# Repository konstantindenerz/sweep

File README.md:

# Sweep

## Hint to this repo

The reason for this fork is the custom themed `Sweep High (Synthwave)`:

## Original

| Front | Back |
| :---: | :---: |
|  |  |

<span>

</span>

## What is sweep?

Sweep is a version of the more fabulous [Ferris](https://github.com/pierrechevalier83/ferris) by [Pierre Chevalier](https://github.com/pierrechevalier83/) that uses a daughter board like a promicro, elite-c, bit-c, nice!nano etc. instead of using onboard components.

## What are the different types?

| Device | On/Off Switch<sup>[1]</sup> | Reversible PCB<sup>[2]</sup> | Choc V1 | Choc V2 | Choc Mini | MX & Alps | Choc Spacing<sup>[3]</sup> | Tenting<sup>[4]</sup> | Hot Swap |
| :--- | :---: | :---: | :---: | :---: | :---: | :---: | :---: | :---: | :---: |
| Sweep2.x          | ✔ |   | ✔ |   |   |   | ✔ | ✔ | Mill-Max (optional) |
| Sweep Bling LP    | ✔ |   | ✔ |   |   |   | ✔ | ✔ | Kailh (required) |
| Sweep Bling MX    | ✔ | ✔ |   |   |   | ⚠<br/><sup>[5]</sup> |   | ✔ | Kailh (required) |
| Sweep High        | ✔ |   | ✔ | ✔ |   | ✔ |   | ✔ |
| Sweep Half Swept  | ✔ | ✔ | ✔ |   |   |   | ✔ | ✔ | Mill-Max (optional) |
| Sweep Compact Low |   | ✔ |   |   | ✔ |   | ✔ |   |

> Note: All versions support bluetooth with Nice!Nano

*<sup>[1]</sup> An on/off switch is recommended for bluetooth builds.*  
*<sup>[2]</sup> With a reversible PCB it's easier to make mistakes during assembly, but it allows you to purchase less boards.*  
*<sup>[3]</sup> Choc spaced boards have the switches in a tighter grid. This provides a better final look but is only compatible with some choc keycaps. (e.g. MBK)*  
*<sup>[4]</sup> Supports splitkb's [tenting puck.](https://splitkb.com/products/tenting-puck?_pos=1&_psq=tenting%20&_ss=e&_v=1.0)*  
*<sup>[5]</sup> MX + kailh hotswap ONLY. Alps are NOT supported.*  

* Sweep2 - Recommended Choc v1 board with all the features.
* Sweep Bling MX - An MX only Sweep that features Kailh's hotswap sockets and a stacked case.
* Sweep High - Same as the Sweep2 but trades choc spacing for compatibility with more switches and keycaps.
* Sweep Half Swept - Half of a Sweep2 with double pro-micro footprint (letting you avoid having one daughter-board flipped upside-down)
* Sweep Compact Low - The only version that supports Choc minis.

## Components list

To build and use a Sweep you will need:

* 1x PCB Kit
* 2x promicro compatible boards or 2 nice!nanos.
* 34 switches of a compatible type (refer to the compatibility table)
* 34 keycaps
* 2x reset switches (optional; [B3U-1000P(M)](https://github.com/davidphilipbarr/Sweep/issues/20))
* Some little rubber feet/bumpers
* 2x power switches (optional if supported; MSK 12C02)
* 1x TRRS (not TRS!) cable (wired build only)
* 2x TRRS Jack [PJ-320A] (wired build only)
* 1 USB Cable (depends on your micro-controller choice)

## How do I make this thing?

## Firmware

The firmware can be found [with the Ferris  firmware as part of QMK](https://github.com/qmk/qmk_firmware/tree/master/keyboards/ferris/sweep).

Firmware for zmk and bluemicro_ble is called ["Cradio"](https://zmk.dev/docs/hardware/).

## Who made this?

* [Pierre Chevalier](https://github.com/pierrechevalier83)
* [David Barr](https://github.com/davidphilipbarr)
* [Ibnu Daru Aji](https://github.com/ibnuda/)
* [Duccio](https://github.com/duckyb)

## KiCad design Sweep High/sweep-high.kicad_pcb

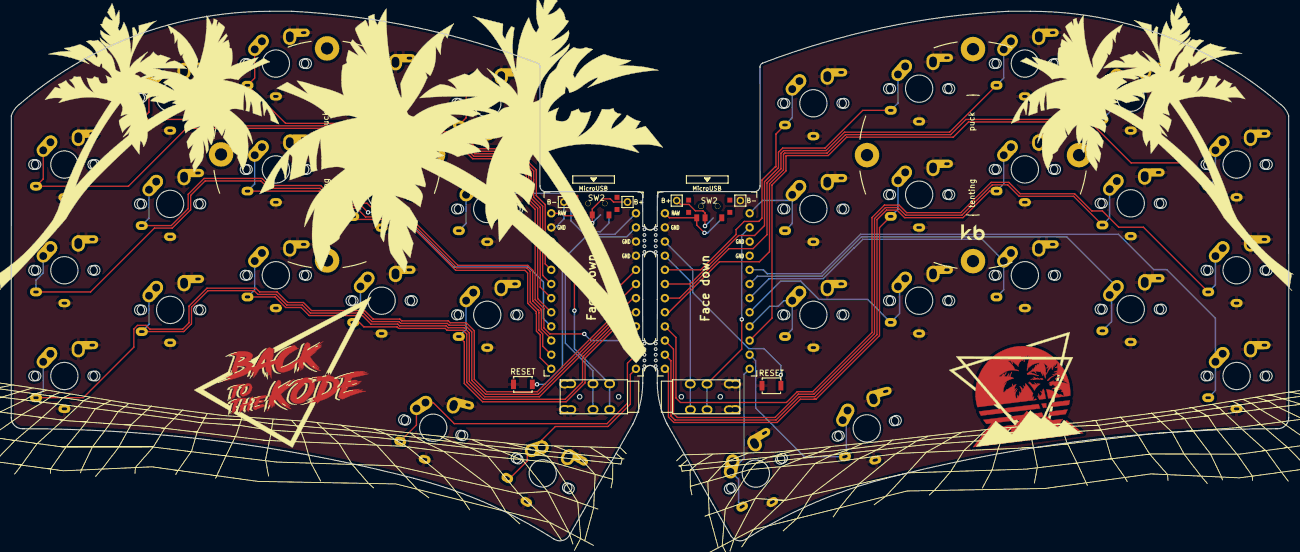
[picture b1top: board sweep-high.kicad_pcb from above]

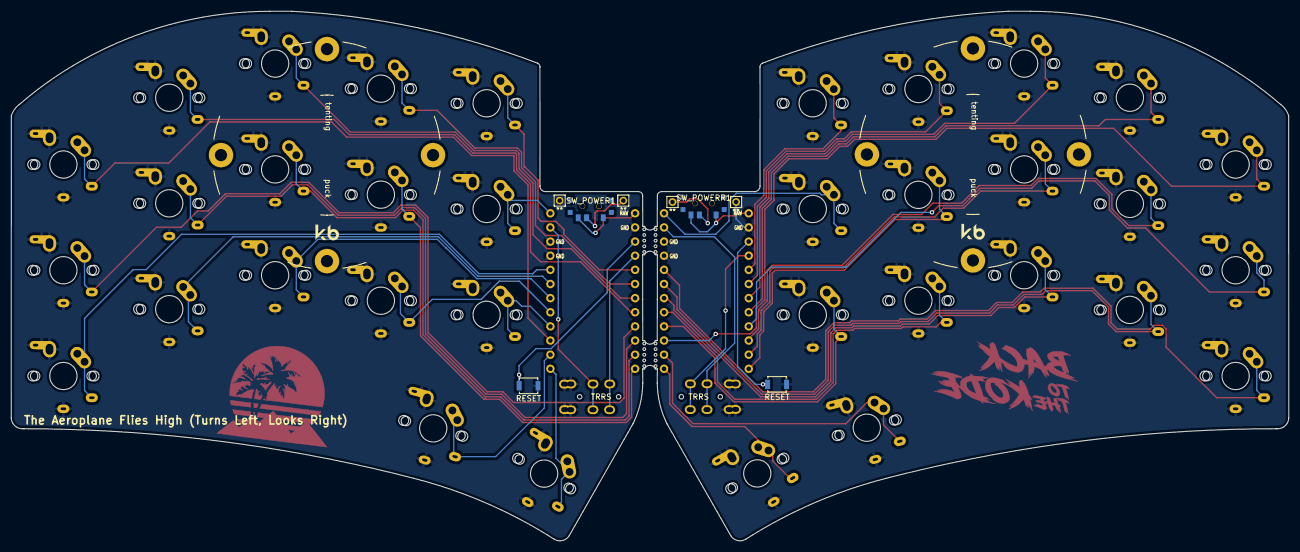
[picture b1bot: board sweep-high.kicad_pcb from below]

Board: 2 copper layers, 229.5 x 95.2 mm, 52 parts (4 on the bottom side), 43 nets.

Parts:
B+: MountingHole_Pad; 1pin_conn
B+#2: MountingHole_Pad; 1pin_conn
B-: MountingHole_Pad; 1pin_conn
B-#2: MountingHole_Pad; 1pin_conn
J1, J2: AudioJack4dpb; TRRS-PJ-DPB2
RSW1, RSW1#2, RSW2, RSW2#2: SW_Push; SW_SPST_B3U-1000P
SW2, SW2_r1, SW3, SW3_r1, SW4, SW4_r1, SW5, SW5_r1, SW6, SW6_r1, SW7_r1, SW8, SW8_r1, SW9, SW9_r1, SW10, SW11, SW11_r1, SW12, SW12_r1, SW13_r1, SW14, SW15, SW15_r1, SW16, SW16_r1, SW17, SW17_r1, SW18, SW18_r1, SW20, SW20_r1, SW21, SW21_r1: SW_Push; keyswitch_cherrymx_alps_choc12_slots_1u
SW2#2, SW2#3: SW_SPDT; SPDT_C128955r
SW_POWER1: SW_SPDT; SPDT_C128955
SW_POWERR1: SW_SPDT; SPDT_C128955
U1, U2: ProMicro-kbd; ProMicro_v3_min
mouse-bite-5mm-slot, mouse-bite-5mm-slot#2: VAL**; mouse-bite-5mm-slot-with-space-for-track

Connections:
BT+: B+#2.1, SW2#3.2, SW_POWER1.2
BT+_r: B+.1, SW2#2.2, SW_POWERR1.2
Switch1: SW2.1, U1.10
Switch1_r: SW2_r1.1, U2.10
Switch2: SW3.1, U1.17
Switch2_r: SW3_r1.1, U2.17
Switch3: SW4.1, U1.18
Switch3_r: SW4_r1.1, U2.18
Switch4: SW5.1, U1.19
Switch4_r: SW5_r1.1, U2.19
Switch5: SW6.1, U1.20
Switch5_r: SW6_r1.1, U2.20
Switch6: SW8.1, U1.16
Switch6_r: SW7_r1.1, U2.16
Switch7: SW9.1, U1.15
Switch7_r: SW8_r1.1, U2.15
Switch8: SW10.1, U1.14
Switch8_r: SW9_r1.1, U2.14
Switch9: SW11.1, U1.13
Switch9_r: SW11_r1.1, U2.13
Switch10: SW12.1, U1.1
Switch10_r: SW12_r1.1, U2.1
Switch11: SW14.1, U1.5
Switch11_r: SW13_r1.1, U2.5
Switch12: SW15.1, U1.6
Switch12_r: SW18_r1.1, U2.6
Switch13: SW16.1, U1.7
Switch13_r: SW15_r1.1, U2.7
Switch14: SW17.1, U1.8
Switch14_r: SW16_r1.1, U2.8
Switch15: SW18.1, U1.9
Switch15_r: SW17_r1.1, U2.9
Switch16: SW21.1, U1.11
Switch16_r: SW21_r1.1, U2.11
Switch17: SW20.1, U1.12
Switch17_r: SW20_r1.1, U2.12
Switch18: J2.R1, U1.2
Switch18_r: J1.R1, U2.2
gnd: B-.1, B-#2.1, J1.S, J1.T, J2.S, J2.T, RSW1.1, RSW1#2.1, RSW2.1, RSW2#2.1, SW2.2, SW2_r1.2, SW3.2, SW3_r1.2, SW4.2, SW4_r1.2, SW5.2, SW5_r1.2, SW6.2, SW6_r1.2, SW7_r1.2, SW8.2, SW8_r1.2, SW9.2, SW9_r1.2, SW10.2, SW11.2, SW11_r1.2, SW12.2, SW12_r1.2, SW13_r1.2, SW14.2, SW15.2, SW15_r1.2, SW16.2, SW16_r1.2, SW17.2, SW17_r1.2, SW18.2, SW18_r1.2, SW20.2, SW20_r1.2, SW21.2, SW21_r1.2, U1.3, U1.4, U1.23, U2.3, U2.4, U2.23
raw: SW2#2.3, SW2#3.3, SW_POWER1.3, SW_POWERR1.3, U1.24, U2.24
reset: RSW1.2, RSW1#2.2, U1.22
reset_r: RSW2.2, RSW2#2.2, U2.22
vcc: J1.R2, J2.R2, U1.21, U2.21

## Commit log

2022-09-03 feat(synthwave): add palms and sun
2022-09-03 Update gallery (automated)
2022-09-03 changed preview styles
2022-09-03 update preview
2022-09-04 update left side branding
2022-09-04 update left side
2022-09-04 create new sweep high copy with kode theme
2022-09-04 feat(sweep-high-synth): create 3d view
